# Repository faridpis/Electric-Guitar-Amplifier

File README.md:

# Electric-Guitar-Amplifier
Design, simulation, assembly, troubleshooting, and coordination of an electric Guitar amplifier circuit board, including component ordering, soldering, and functional testing.

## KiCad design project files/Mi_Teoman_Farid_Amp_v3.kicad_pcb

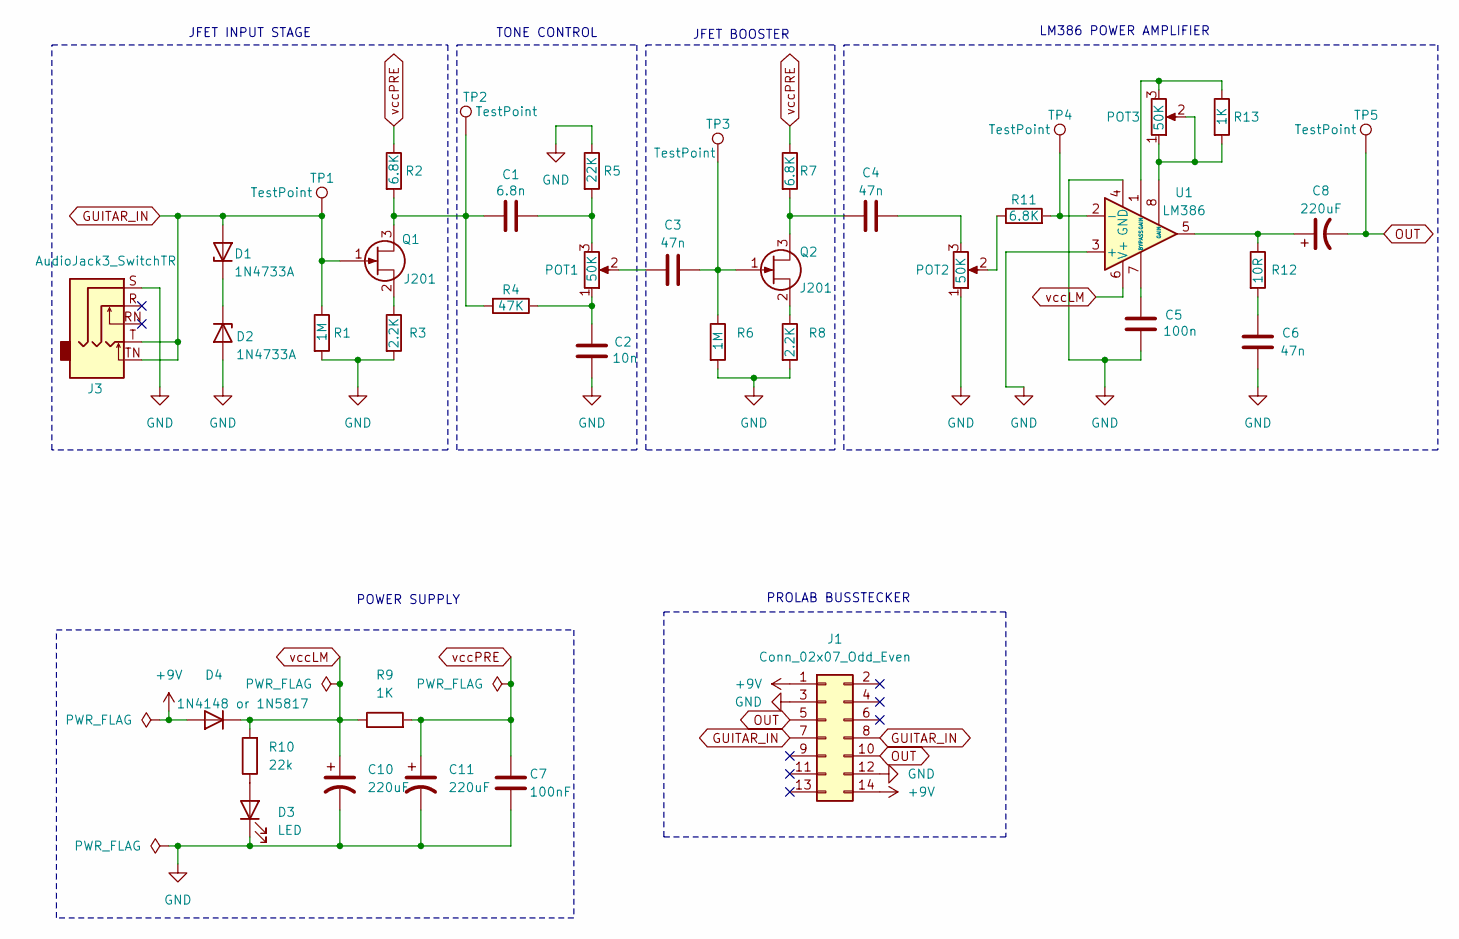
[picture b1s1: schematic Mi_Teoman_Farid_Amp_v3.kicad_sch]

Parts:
C1: 6.8n; C_Disc_D4.3mm_W1.9mm_P5.00mm
C2: 10n; C_Disc_D4.3mm_W1.9mm_P5.00mm
C3, C4, C6: 47n; C_Disc_D4.3mm_W1.9mm_P5.00mm
C5: 100n; C_Disc_D4.3mm_W1.9mm_P5.00mm
C7: 100nF; C_Disc_D4.3mm_W1.9mm_P5.00mm
C8, C10, C11: 220uF; C_Radial_D10.0mm_H12.5mm_P5.00mm
D1, D2: 1N4733A; D_DO-41_SOD81_P10.16mm_Horizontal
D3: LED; LED_D3.0mm_IRBlack
D4: 1N4148 or 1N5817; D_DO-35_SOD27_P7.62mm_Horizontal
J1: Conn_02x07_Odd_Even; Busstecker
J3: AudioJack3_SwitchTR; Jack_3.5mm_CUI_SJ1-3515N_Horizontal
POT1, POT2, POT3: 50K; Potentiometer_Alps_RK163_Single_Horizontal
Q1, Q2: J201; TO-92L_Inline_Wide
R1, R6: 1M; R_Axial_DIN0207_L6.3mm_D2.5mm_P10.16mm_Horizontal
R2, R7, R11: 6.8K; R_Axial_DIN0207_L6.3mm_D2.5mm_P10.16mm_Horizontal
R3, R8: 2.2K; R_Axial_DIN0207_L6.3mm_D2.5mm_P10.16mm_Horizontal
R4: 47K; R_Axial_DIN0207_L6.3mm_D2.5mm_P10.16mm_Horizontal
R5: 22K; R_Axial_DIN0207_L6.3mm_D2.5mm_P10.16mm_Horizontal
R9, R13: 1K; R_Axial_DIN0207_L6.3mm_D2.5mm_P10.16mm_Horizontal
R10: 22k; R_Axial_DIN0207_L6.3mm_D2.5mm_P10.16mm_Horizontal
R12: 10R; R_Axial_DIN0207_L6.3mm_D2.5mm_P10.16mm_Horizontal
TP1, TP2, TP3, TP4, TP5: TestPoint; TestPoint_Pad_D2.0mm
U1: LM386; DIP-8_W7.62mm_Socket_LongPads

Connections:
+9V: D4.2 (A), J1.1, J1.14
GND: C2.2, C5.2, C6.2, C7.2, C10.2, C11.2, D2.2 (A), D3.1 (K), J1.3, J1.12, J3.S, POT2.1, R1.2, R3.2, R5.1, R6.2, R8.2, U1.3 (+), U1.4 (GND)
GUITAR_IN: D1.2 (A), J1.7, J1.8, J3.T, J3.TN, Q1.1 (G), R1.1, TP1.1
unnamed: C1.2, POT1.3, R5.2
unnamed: C2.1, POT1.1, R4.1
unnamed: C3.1, POT1.2
unnamed: C4.2, POT2.3
unnamed: C6.1, R12.2
unnamed: C8.1, R12.1, U1.5
unnamed: D1.1 (K), D2.1 (K)
unnamed: D3.2 (A), R10.1
unnamed: POT2.2, R11.1
unnamed: POT3.1, POT3.2, R13.2, U1.8 (GAIN)
unnamed: POT3.3, R13.1, U1.1 (GAIN)
unnamed: C1.1, Q1.3 (D), R2.2, R4.2, TP2.1
unnamed: Q1.2 (S), R3.1
unnamed: C4.1, Q2.3 (D), R7.2
unnamed: C3.2, Q2.1 (G), R6.1, TP3.1
unnamed: Q2.2 (S), R8.1
unnamed: R11.2, TP4.1, U1.2 (-)
unnamed: C5.1, U1.7 (BYPASS)
OUT: C8.2, J1.5, J1.10, TP5.1
vccLM: C10.1, D4.1 (K), R9.1, R10.2, U1.6 (V+)
vccPRE: C7.1, C11.1, R2.1, R7.1, R9.2

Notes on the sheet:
PROLAB BUSSTECKER
LM386 POWER AMPLIFIER
JFET BOOSTER
JFET INPUT STAGE
TONE CONTROL
POWER SUPPLY

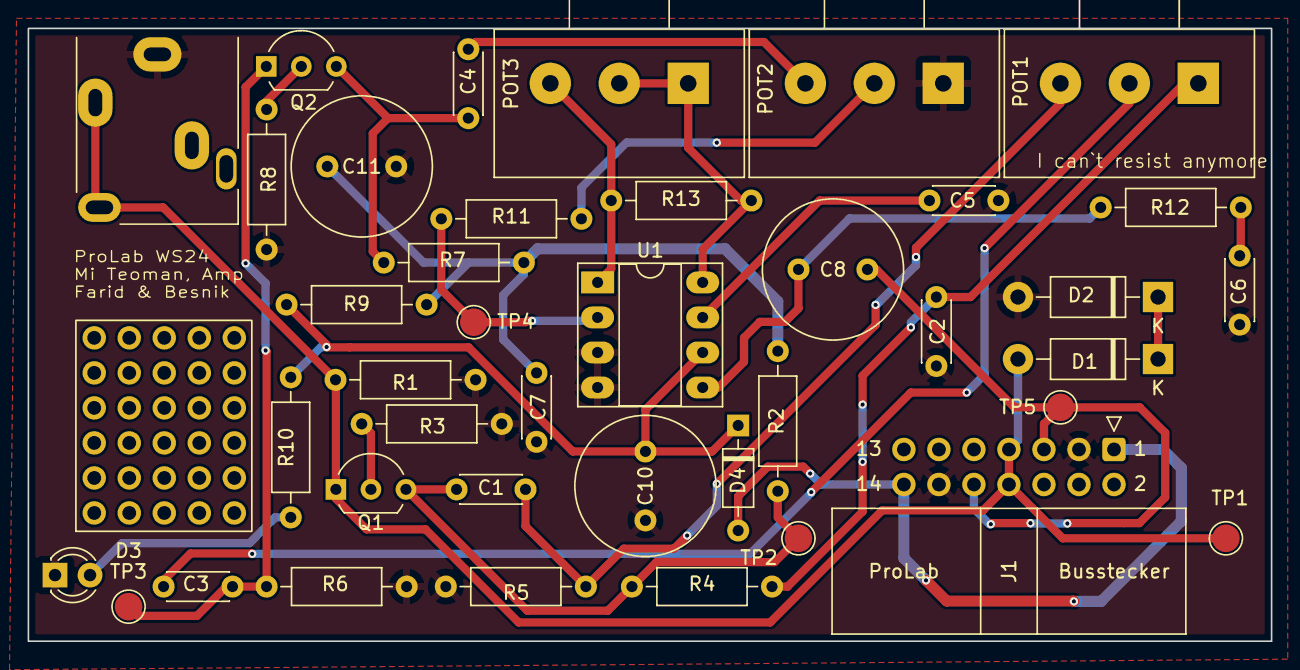
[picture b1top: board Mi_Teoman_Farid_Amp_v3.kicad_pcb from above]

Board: 2 copper layers, 90.2 x 44.5 mm, 40 parts (0 on the bottom side), 24 nets.

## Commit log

2026-05-09 had to use the dev tool to make folders
